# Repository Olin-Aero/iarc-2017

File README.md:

This is the primary repository for the Olin College Aero club's attempt at competing in IARC 2018.

# Running with Docker
## Installing GPU acceleration
<!-- http://wiki.ros.org/docker/Tutorials/Hardware%20Acceleration -->
```
# https://nvidia.github.io/nvidia-docker/
curl -s -L https://nvidia.github.io/nvidia-docker/gpgkey | \
  sudo apt-key add -
curl -s -L https://nvidia.github.io/nvidia-docker/ubuntu16.04/amd64/nvidia-docker.list | \
  sudo tee /etc/apt/sources.list.d/nvidia-docker.list
sudo apt-get update

# https://github.com/NVIDIA/nvidia-docker/wiki/Installation-(version-1.0)
sudo apt-get install nvidia-docker

```

## Starting the container and getting a terminal
```
nvidia-docker run -it --rm \
	--net foo \
	--name devel \
	--env="DISPLAY" \
	--env=UIUSER=(whoami) \
	--volume="/etc/group:/etc/group:ro" \
	--volume="/etc/passwd:/etc/passwd:ro" \
	--volume="/etc/shadow:/etc/shadow:ro" \
	--volume="/etc/sudoers.d:/etc/sudoers.d:ro" \
	--volume="/tmp/.X11-unix:/tmp/.X11-unix:rw" \
	ros:iarc-2017-devel   \
	bash
```

## Getting more terminals
```
docker exec -it devel bash
```

## Running GUI tools
```
docker exec devel ui rviz
# or
docker exec devel ui rqt
# .... etc
```

# Installation instructions

This repository includes a dependency on gstreamer, a program for low-latency network video streaming. You must install it for the program to build.

	sudo apt-get install libgstreamer1.0-dev libgstreamer-plugins-* gstreamer1.0-libav* gstreamer1.0-plugins*
  
All other dependencies can be installed using `rosdep` and `pip`:

    rosdep install --ignore-src --from-paths $(rospack find iarc_main)/.. -y
    pip install -r $(rospack find iarc_main)/../requirements.txt

Finally, `catkin_make` can be used to build the code

	cd ~/catkin_ws && catkin_make

Copy camera calibration to your ROS install

	mkdir -p ~/.ros/camera_info && cp $(rospack find iarc_vision)/calibration/* ~/.ros/camera_info/

# Useful Commands
As of 12/18/2017, the following commands are useful to run the code on an AR Drone

	roscore
	roslaunch iarc_main backbone.launch
	roslaunch iarc_main ardrone_interface.launch
	
	roslaunch iarc_vision apriltags.launch
	rosrun iarc_main ardrone_keyboard.py cmd_vel:=/teleop/cmd_vel

	# One of the following three...
	rostopic pub /arbiter/activate_behavior std_msgs/String "teleop" -1
	rostopic pub /arbiter/activate_behavior std_msgs/String "goto_click" -1
	rostopic pub /arbiter/activate_behavior std_msgs/String "follow" -1
	
	rqt
	rviz
	rostopic echo /ardrone/navdata/batteryPercent

	rosbag record -a -x ".*image_raw\$|.*tag_detections.*"

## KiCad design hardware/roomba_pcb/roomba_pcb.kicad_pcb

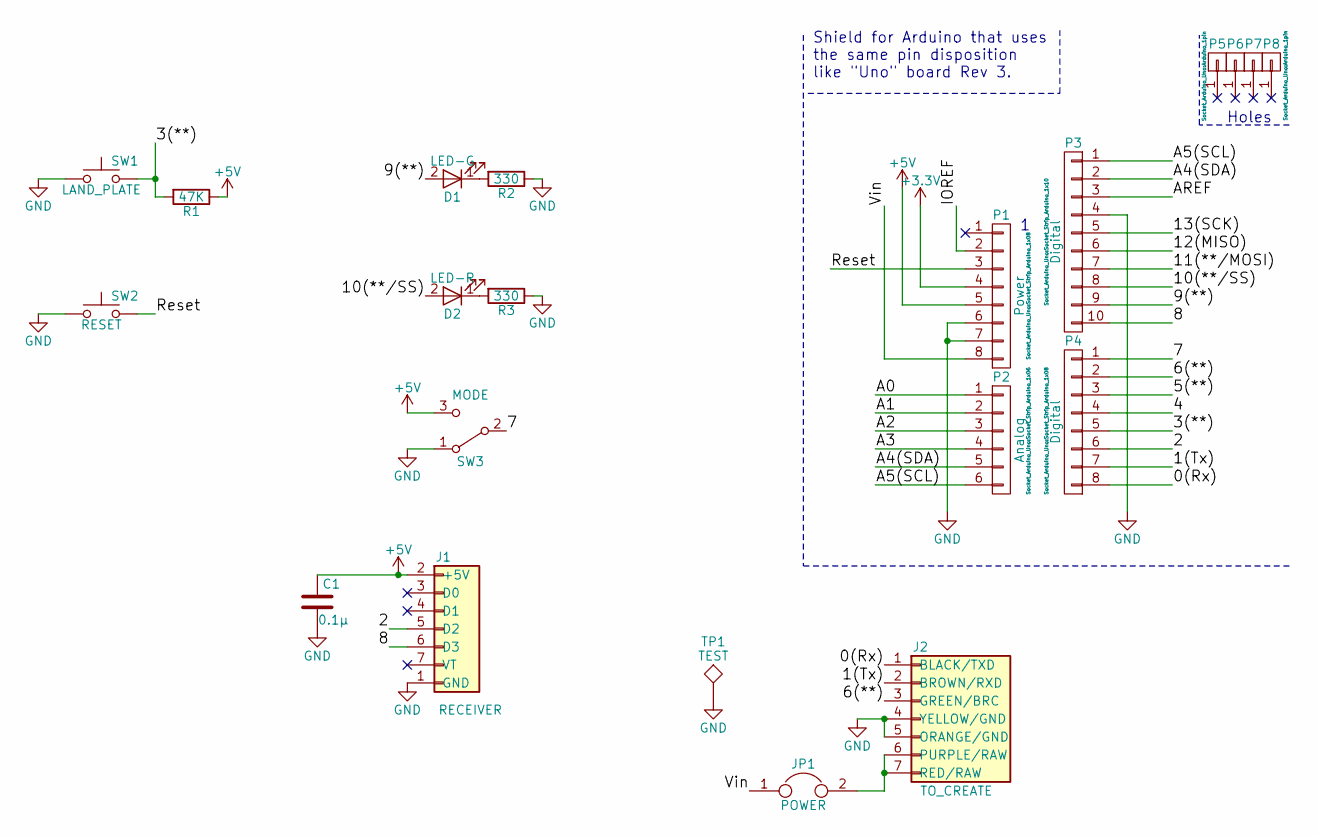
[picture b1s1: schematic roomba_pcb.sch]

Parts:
C1: 0.1µ; C_0603
D1: LED-G; LED_0805
D2: LED-R; LED_0805
J1: RECEIVER; Receiver_IARC
J2: TO_CREATE; Pin_Header_Straight_1x07_Pitch2.54mm
JP1: POWER; Pin_Header_Straight_1x02_Pitch2.54mm
P1: Power; Socket_Strip_Arduino_1x08
P2: Analog; Socket_Strip_Arduino_1x06
P3: Digital; Socket_Strip_Arduino_1x10
P4: Digital; Socket_Strip_Arduino_1x08
P5, P6, P7, P8: CONN_01X01; Arduino_1pin
R1: 47K; R_0603
R2, R3: 330; R_0603
SW1: LAND_PLATE; Pin_Header_Straight_1x02_Pitch2.54mm
SW2: RESET; SW_SPST_B3U-1000P
SW3: MODE; Pin_Header_Straight_1x03_Pitch2.54mm
TP1: TEST; Pin_Header_Straight_1x01_Pitch2.54mm

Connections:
+3V3: P1.4
+5V: C1.1, J1.2 (+5V), P1.5, R1.1, SW3.3 (C)
/0(Rx): J2.1 (BLACK/TXD), P4.8
/1(Tx): J2.2 (BROWN/RXD), P4.7
/2: J1.5 (D2), P4.6
/3(**): P4.5, R1.2, SW1.2
/4: P4.4
/5(**): P4.3
/6(**): J2.3 (GREEN/BRC), P4.2
/7: P4.1, SW3.2 (B)
/8: J1.6 (D3), P3.10
/9(**): D1.2 (A), P3.9
/10(**/SS): D2.2 (A), P3.8
/11(**/MOSI): P3.7
/12(MISO): P3.6
/13(SCK): P3.5
/A0: P2.1
/A1: P2.2
/A2: P2.3
/A3: P2.4
/A4(SDA): P2.5, P3.2
/A5(SCL): P2.6, P3.1
/AREF: P3.3
/IOREF: P1.2
/Reset: P1.3, SW2.2
/Vin: JP1.1, P1.8
GND: C1.2, J1.1 (GND), J2.4 (YELLOW/GND), J2.5 (ORANGE/GND), P1.6, P1.7, P3.4, R2.1, R3.1, SW1.1, SW2.1, SW3.1 (A), TP1.1
unnamed: D1.1 (K), R2.2
unnamed: D2.1 (K), R3.2
unnamed: J2.6 (PURPLE/RAW), J2.7 (RED/RAW), JP1.2

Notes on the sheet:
Holes
Shield for Arduino that uses the same pin disposition like "Uno" board Rev 3.

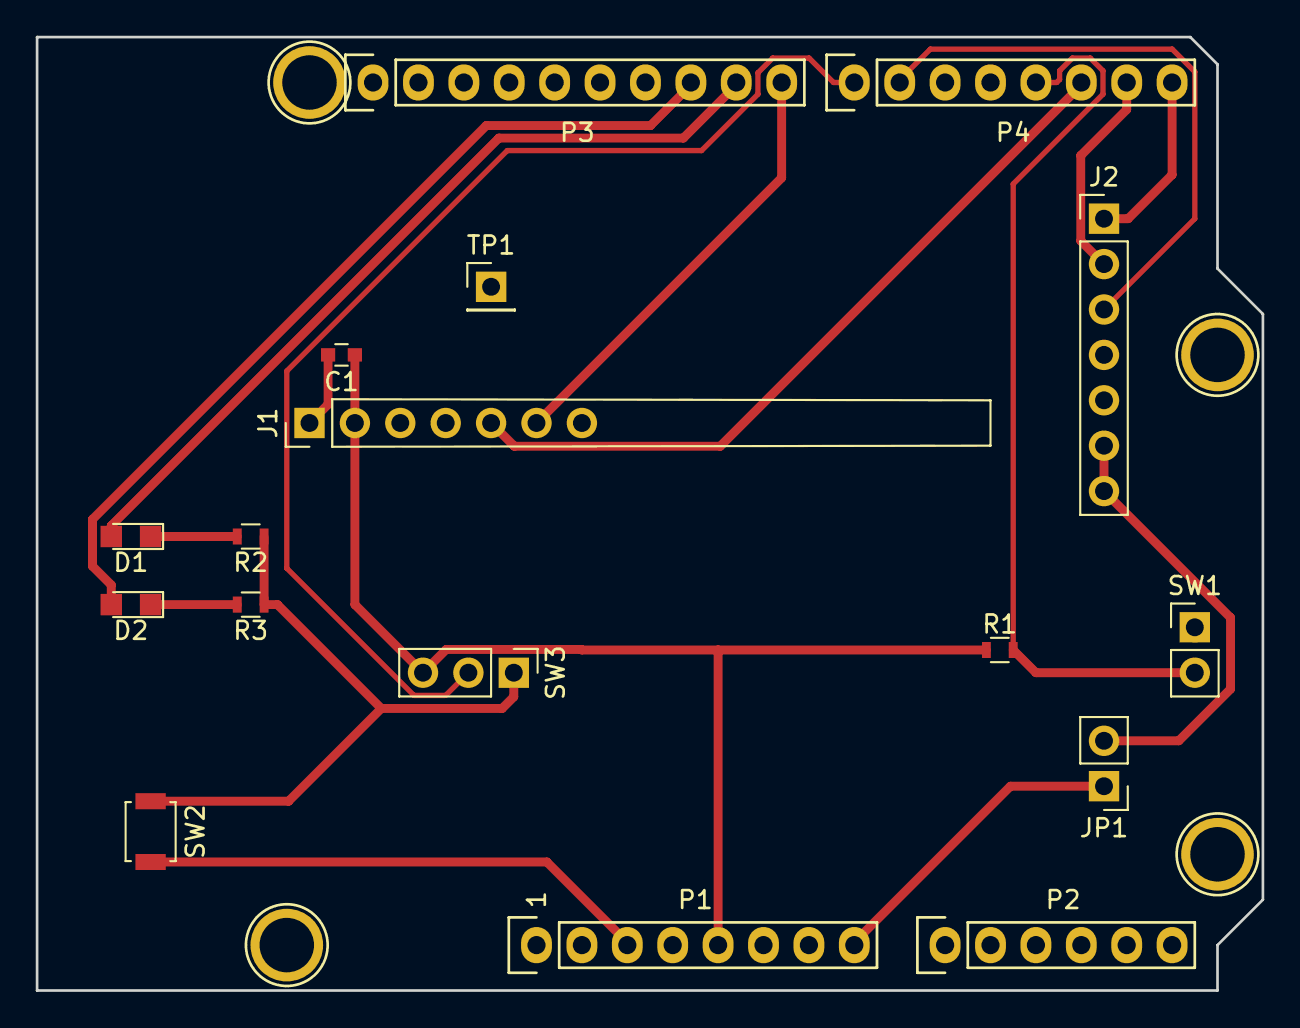
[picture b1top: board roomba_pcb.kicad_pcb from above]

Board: 2 copper layers, 68.6 x 53.3 mm, 21 parts (0 on the bottom side), 18 nets.

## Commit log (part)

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2017-10-14 refactoring as catkin package, improving roomba visuals
2017-10-15 setup basic world
2017-10-16 Remapped apriltag tf frame to "target"
2017-10-16 working image gen with rotations, translations, and altitude - no annotations yet
2017-10-16 Added readme for predandstrat
2017-10-16 new urdf, because the old one was very inaccurate and unwieldy. Works.
2017-10-16 really just a bad idea for spawning roombas ...
2017-10-16 need to setup proper tf.
2017-10-16 we'll see.
2017-10-17 replaced visual-plugin markers with box mesh
2017-10-17 starting on obstacle roomba, as well as universal roomba class
2017-10-19 Create follow behavior function linked with arbiter
2017-10-19 Edit function descriptions for follow_roomba.py
2017-10-23 updating code
2017-10-23 Bring a for loop outside of follow_roomba function
2017-10-23 BrFix follow roomba bug
2017-10-23 moving code
2017-10-23 bug with no collision detection?
2017-10-23 improved target roomba impl., still need to fix obstacle roomba dynamic pole height
2017-10-24 updating spawn script
2017-10-24 synced initialization after 5 sec.
2017-10-24 well, you should probably figure out roomba tfs programmatically anyways ...
2017-10-24 fixed tf in a workaround.
2017-10-25 adding PushRoomba
2017-10-25 Added particle filter from CompRobo 2017
2017-10-26 added top plate and verified collision still works
2017-10-26 turns out, no reason to supply the god-awful collision link names in urdf (model plugin handles it)
2017-10-30 Added tum_simulator library
2017-10-30 transfering neural network code to desktop
2017-10-30 Added message for RoombaSightings as standard output of vision algorithms
2017-10-30 Added Vision Package
2017-10-30 Added MIT License
2017-10-30 ROS to OpenCV example script
2017-10-30 added color tracking script
2017-11-01 Added strategy structure
2017-11-02 made params work in sim2d
2017-11-02 Made a PCB!
2017-11-03 Modified strategy
2017-11-03 Made obstacles configurable
2017-11-03 Fixed merge conflict
2017-11-03 commented where I need to add publishers
2017-11-04 Adding current heatmap code: Runs fine; graph is not displaying colors correctly
2017-11-05 Created a score evaluation funciton for roombas
2017-11-06 support strafing
2017-11-06 added header to contact me
2017-11-06 Drone push button and land in front
2017-11-06 Imported ROSlaunch file for USB camera and adjusted to our parameters
2017-11-06 Added (poor) calibration data for laptop camera
2017-11-06 Need to fix follow PID
2017-11-06 Created initial apriltag rebroadcaster into standardized RoombaSighting format
2017-11-06 Add comments and documentation for Drone.py
2017-11-08 Added requirements.txt for state machine dependencies
2017-11-08 Updated fiveSecSim
2017-11-08 Reformatted file
2017-11-08 Added turn timer to Roomba message
2017-11-08 Added chooseAction method to strategy
2017-11-09 cleaned up angle_predictor
2017-11-09 supports 3D TF. Careful : no crashing into ground supported
2017-11-09 Publishing hitting obsticle pole failure condition
2017-11-09 Reworked height handling in Drone class to use cmd_pos conventions
2017-11-11 Worked on modifying the messages
2017-11-14 Made better messages betteR
2017-11-15 Working on heatmap_khang.py from heatmap.py by Lydia
2017-11-16 Added libraries for electronics
2017-11-16 Added code to launch ardrone interface with bottom camera active
2017-11-16 Added calibration files for ardrone cameras
2017-11-21 custom messages
2017-11-30 Added comments to apriltag rebroadcaster
2017-11-30 updating HeatMap
2017-11-30 Pushing unfinished covariance matrix work
2017-11-30 Added static transform for base_link on AR drone
2017-11-30 Tuned PID following for tests, resulted in first successful tag follow!
2017-12-04 Functional grid tracking code, roughly calibrated on USB camera
2017-12-04 Added ddynamic_reconfigure library
2017-12-04 Fixed bug with ddyn config
2017-12-04 Added auto-stop to arbiter when new behavior selected
2017-12-05 Made the action subset list more complete
2017-12-06 Changed PID controller to use latest available drone location, even when the target's location is a little bit old.
2017-12-06 more filter stuff
2017-12-06 slack-reported version
2017-12-06 implemented particle-matching (to some degree of usefulness)
2017-12-06 working UKF
2017-12-06 splitting
2017-12-06 TODO : fix flickering problem
2017-12-06 playable demo now
2017-12-06 better filtering architecture; TODO : ultimately do the TODOs
2017-12-06 now modelling target roombas
2017-12-06 more refactoring
2017-12-06 in the middle of improving target particle prediction; don't forget to change step()
2017-12-06 Handled dependency installation better for filter
2017-12-07 Recorded ROSBAG of grid tracking, the actual data in on Public.
2017-12-10 Commiting working, commented version of futureSim with events implemented.
2017-12-11 making ROS interface; also converting all previous pose definitions as np.array instead of a custom class, to avoid confusion.
2017-12-14 Fixed message build order for iarc_sim_engine
2017-12-14 Successful test with following target
2017-12-14 Added code to publish target Roomba
2017-12-14 Altered strategy to fallback to teleop after 5 seconds
2017-12-14 Squashed several errors, done for the night.
2017-12-18 Expo thing
2017-12-18 Added hints and useful commands to the README
2018-01-30 Archived old heatmap code
2018-01-30 Added test case back into five second simulator
2018-01-30 Removed PredictionEngine
2018-01-30 Added comments to strategy.py
2018-01-30 Removed ChangeHeight
2018-01-30 Removed some redundant files
2018-02-06 Created catkin package for forebrain
2018-02-06 Added dependency on iarc_forebrain
2018-02-06 adding gazebo simulation interface and ROS integration
2018-02-06 Began creating new better-designed forebrain program
2018-02-06 basic RVIZ visualization on algorithm performance, currently there seems to be a bug on UKF manager
2018-02-06 still struggling with strange discrepancy issue in estimates not moving
2018-02-07 fixed bug with non-moving prediction (related to processing old messages), added launch config
2018-02-10 #81 added comments
2018-02-10 Added "fly square" test strategy, and tested in simulator progress on #81
2018-02-10 Adjusted default tolerance to 20cm #81
2018-02-10 Adjustments as tested on the Parrot drone : #81
2018-02-11 Adds automatic republishing as an option for namespaces handled by the Arbiter. Progress towards #81
2018-02-11 Changed takeoff and landing methods to be blocking be default. Made simulator work with those methods. Progress towards #81
2018-02-13 Added activate publisher to ardrone_keyboard
2018-02-13 Fixed bugs to get simulator of Roomba following working
2018-02-13 fixed non-moving particles bug on non-ros interface | possibly successful fusion of model vs. observation;
2018-02-13 added README
2018-02-13 Added first attempt at landing-in-front code
2018-02-13 Added new cmd_vel_alt input type to the Arbiter to handle cases where we want PID control of altitude, but manual control of x-y-theta velocity
2018-02-20 removed deprecated code and stuff
2018-02-20 Changed forebrain to listen directly to visible_roombas until the Filter is merged
2018-02-20 Fixing IMU integration
2018-02-21 test showing pdf figs
    test #2
    nevermind on embedded pdf
    Added link to pipeline visuals
2018-02-28 massive update in observability, now accounts for camera parameters and drone position
2018-02-28 deprecating some old stuff, including p()
2018-02-28 added relevant changes based on Eric's comments
2018-02-28 reconfigured roombasighting -> roombalist
2018-02-28 Published transforms from filter
2018-03-02 Added dependency-based ROS package thing
2018-03-03 adding roomba models
2018-03-03 adding color tracking file
2018-03-03 updating ColorTracking
2018-03-03 added the rectangle around plate
2018-03-03 adding image 2
2018-03-04 Update README.md
    Added -y flag to rosdep instructions to simplify installation
2018-03-04 Added .devel dockerfile for fast rebuild cycles
2018-03-06 Added support for GUI programs like rqt and rviz
2018-03-06 added scratch
2018-03-06 Modified code to "work" with an Arduino Uno.
2018-03-06 fixed code with HSV
2018-03-06 Made GPU acceleration work on x86 with nvidia-docker v1
2018-03-06 fixed confusing comments
2018-03-06 adding readme for reproducing stuff. Why is grid finding in iarc_main anyways?
2018-03-10 adding centers of boxes
2018-03-10 roombas are a lot harder than neatos, accurate to within +- 30 deg
2018-03-10 Add green detection
2018-03-10 Add to do for find_bounding_boxes func
2018-03-13 adding code to compute one of two directions
2018-03-13 fixed quaternion error, works!
2018-03-13 Refactor code
2018-03-13 Change variable names
2018-03-13 Angle of roomba
2018-03-13 Fix arctan function
2018-03-16 writing blog post
2018-03-22 fixed line misalignment issue and some code restructuring
2018-03-27 restructure code format
2018-03-27 restructuring code
2018-03-31 adding heading
2018-03-31 preliminary exploration
2018-03-31 characterization
2018-03-31 now with ROS interface
2018-04-03 Added 1st draft of 45-degree turn routine
2018-04-03 somewhat working; the filter needs to be improved, mostly. The explorer is running OK-ish
2018-04-07 adding ChooseTarget and integration with forebrain.py
2018-04-07 fix import
2018-04-07 general improvements to 2d sim, and filter working nicely with sim2d now
2018-04-07 explorer probably works now
2018-04-09 fixing quaternion
2018-04-10 added explore
2018-04-14 Changed topic names for takeoff and landing
2018-04-16 Began work on pixhawk connector
2018-04-16 Added launch file for px4 from laptop
2018-04-16 Added takeoff and landing handlers
2018-04-21 Added untested code to compute and publish vehicle location
2018-04-24 made the roomba publishing work
2018-04-24 Successfully sending position over mavros
2018-04-25 adding list
2018-04-25 Added Odometry publishing
2018-04-25 Made odometry publishing work
2018-04-26 compressed to image
2018-04-28 Updating ColorTracking for Babson Gym Testing
2018-05-01 more clear parameter description sim->gz_obs
2018-05-01 remove init time to sync with time
2018-05-02 fixing heading problem
2018-05-03 tum_simulator cmake issues
2018-05-03 comments on TODOs, testing complete
2018-05-03 rebase + refactor into iarc_vision from iarc_main
2018-05-03 additional comments on filter3 todos
2018-05-08 attempt to apply adaptive area thresholding based on height
2018-05-08 digitalWrite pin d2
2018-05-08 removed area-related todo
2018-05-08 added noisy odometry + grid finder filtering
2018-05-08 gridfinder parametrization
2018-05-12 fixing covariance heading stuff. there seems to be some error when testing, so I'm not confident that the fix worked.
2018-05-12 Began creating everything.launch file
2018-05-12 Triggered pixhawk_connector to publish initial transform
2018-05-12 Made sure Arbiter doesn't start processing callbacks before the dynamic configuration is ready.
2018-05-12 Slowed down logging of calculated poses
2018-05-12 Fixed exceptions again
2018-05-12 Fixed keyboard controller to work with both kinds of drones
2018-05-13 added bottom_wide
2018-05-13 minor change regarding odom drift magnitude, noisy odom is still sort-of-incorrect
2018-05-13 attempts to integrate noisy odom, not working that well
2018-05-13 adding instructions
2018-05-13 Changed to use new calibration file
2018-05-13 Added error handling on publish
2018-05-13 Fixed error in logging code
2018-05-14 Fixed merge bugs in colortracking
2018-05-14 Switched to green instead of red
2018-05-14 Detect odometry messages from the future and ignore them
2018-05-14 update republish instructions
2018-05-14 hopefully works
2018-05-14 Added logging for velocity coordinate transformations
2018-05-14 Fixed transform of the camera from base_link
2018-05-14 roomba filter not working that well, needs a fair amount of tweaking, parameter explorations, algorithmic improvements, etc., for this to work under high-error, unstable conditions
